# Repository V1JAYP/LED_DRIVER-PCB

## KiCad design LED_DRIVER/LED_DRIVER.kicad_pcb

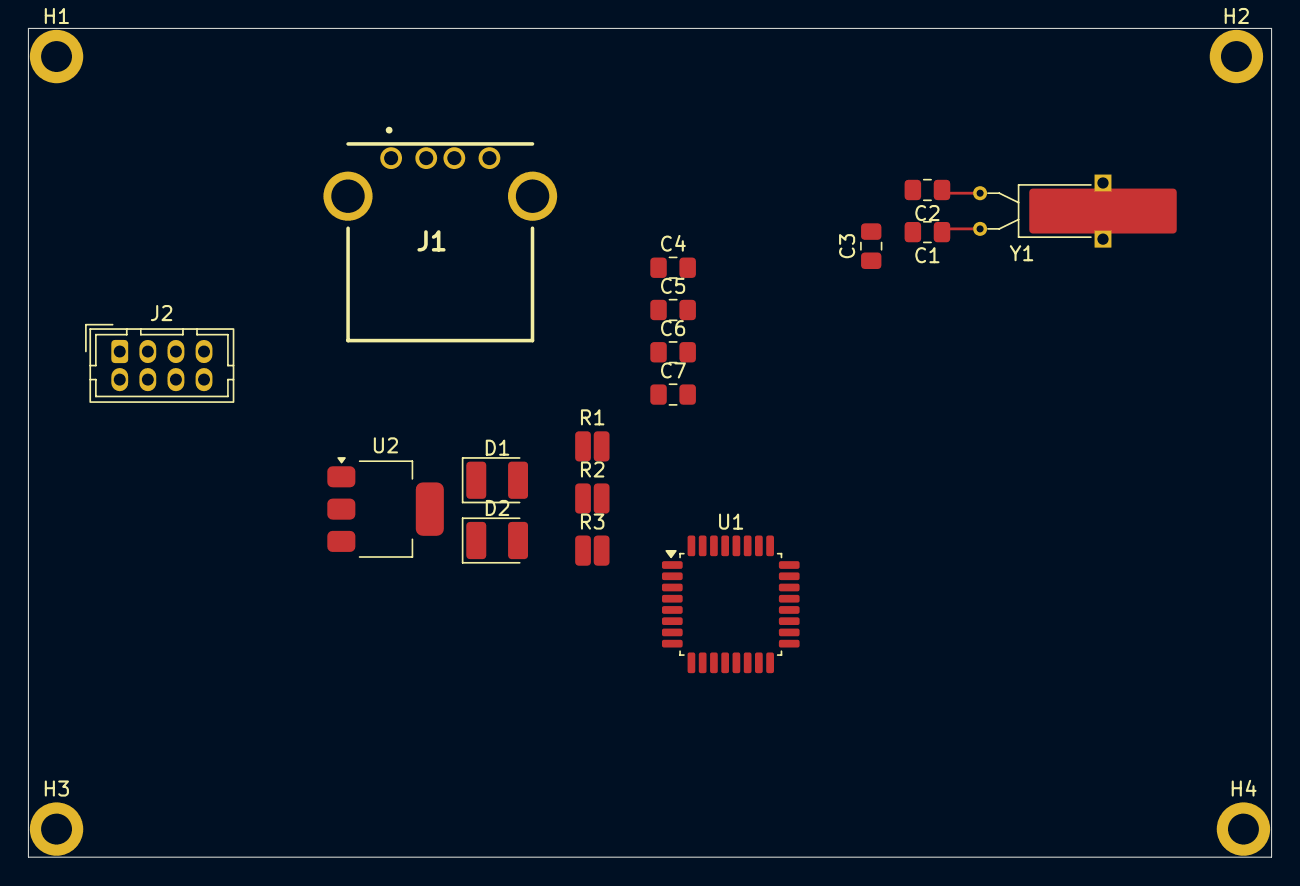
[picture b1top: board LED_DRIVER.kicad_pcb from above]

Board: 2 copper layers, 88.5 x 59.0 mm, 21 parts (0 on the bottom side), 9 nets.

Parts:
C1, C2: 22pF; C_0805_2012Metric_Pad1.18x1.45mm_HandSolder
C3, C4: 0.1uF; C_0805_2012Metric_Pad1.18x1.45mm_HandSolder
C5, C6: 47uF; C_0805_2012Metric_Pad1.18x1.45mm_HandSolder
C7: 4.7uF; C_0805_2012Metric_Pad1.18x1.45mm_HandSolder
D1, D2: D_Schottky; D_1210_3225Metric_Pad1.42x2.65mm_HandSolder
H1, H2, H3, H4: MountingHole_Pad; MountingHole_2.2mm_M2_DIN965_Pad
J1: USB_A; 6364372-1
J2: Conn_02x04_Odd_Even; Hirose_DF11-8DP-2DSA_2x04_P2.00mm_Vertical
R1, R2: 68; R_0508_1220Metric_Pad1.12x2.15mm_HandSolder
R3: 2.2k; R_0508_1220Metric_Pad1.12x2.15mm_HandSolder
U1: ATmega328P-A; TQFP-32_7x7mm_P0.8mm
U2: AMS1117; SOT-223-3_TabPin2
Y1: Crystal; Crystal_AT310_D3.0mm_L10.0mm_Horizontal_1EP_style2

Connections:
3V3D: C3.1, C4.1, C5.1, U1.4 (VCC), U1.6 (VCC), U1.18 (AVCC), U2.2 (VO)
5VD: C6.1, C7.2, J1.1 (VBUS), R3.1, U2.3 (VI)
GND: C1.2, C2.2, C3.2, C4.2, C5.2, C6.2, C7.1, D1.2 (A), D2.2 (A), H1.1 (1_1), H2.1 (1_1), H3.1 (1_1), H4.1 (1_1), J1.4 (GND), U1.3 (GND), U1.5 (GND), U1.21 (GND), U2.1 (ADJ)
unnamed: D1.1 (K), J1.3 (D+), R1.1, R3.2
unnamed: D2.1 (K), J1.2 (D-), R2.1
unnamed: C1.1, U1.7 (XTAL1/PB6), Y1.1
unnamed: C2.1, U1.8 (XTAL2/PB7), Y1.2
USBD+: R1.2, U1.13 (PB1), U1.32 (PD2)
USBD-: R2.2, U1.12 (PB0)
